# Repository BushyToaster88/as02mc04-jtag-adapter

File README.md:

# AS02MC04 JTAG adapter for the Digilent JTAG-HS3

A small board that lets a Digilent JTAG-HS3 plug straight onto the 6-pin JTAG header (J4)
of the Alibaba Cloud AS02MC04 FPGA card (label PN YZQT-02337-101, Xilinx Kintex UltraScale+ XCKU3P).

> **Status, 2026-11-13:** the first five boards are on order from JLCPCB and have not arrived.
> Nothing here has been tested on real hardware yet. Write-up:
> <https://www.exulan.com/blog/2026-11-13-as02mc04-jtag-adapter>

The HS3 has a 2x7, 2.00 mm Xilinx plug. The card has a 1x6, 2.54 mm pin header with a different
pin order and no keying. This board converts one to the other, takes the HS3's reference voltage
from the card's own 1V8 pin, and survives being plugged on the wrong way round.

| | |
|---|---|
| Revision | C, 2026-11-11 |
| Board | 24.0 x 29.55 mm, 2 layers, 1.6 mm, all parts on one side |
| Made by | JLCPCB, economic assembly, arrives ready to use (no soldering) |
| Card side | J2, right-angle 1x6 socket on the bottom edge, plugs onto J4 |
| Probe side | J1, keyed and shrouded Molex 87832-1420, the header the HS3 is made for |
| JTAG voltage | 1.8 V only, taken from the card |

## How it sits on the card

The adapter stands upright on J4. The side with the parts (front) points away from the card,
past its rear edge, and so does the HS3. The side with the pin names (back) faces the heatsink.

J4 is at the rear end of the card (the end away from the bracket), on the heatsink side. Seen from
that side with the rear edge toward you, the card's silkscreen reads `GND TDI TDO TDK TMS 1`, with
`1V8` printed sideways next to pin 1. `TDK` is the card's spelling of TCK.

Space needed: the top of the adapter is about 32 mm above the card, and the HS3 sticks out roughly
35 mm past the card's rear edge, plus the USB plug and the bend of its cable.

## Pin map

| HS3 / J1 pin | Signal | Through | J2 pin | Card J4 pin | Card silkscreen |
|---|---|---|---|---|---|
| 2 | VREF (HS3 buffer supply) | R9, 4.7 ohm 0.75 W | 1 | 1 | 1V8 |
| 4 | TMS | R1, 22 ohm | 2 | 2 | TMS |
| 6 | TCK | R2, 22 ohm | 3 | 3 | TDK |
| 8 | TDO (card to HS3) | R3, 22 ohm | 4 | 4 | TDO |
| 10 | TDI | R4, 22 ohm | 5 | 5 | TDI |
| 1, 3, 5, 7, 9, 11, 13 | GND | Q1 (reverse protection) | 6 | 6 | GND |
| 12, 14 | not connected | | | | |

## Check the connector pitch first

`docs/pitch_gauge.pdf` is a 1:1 print sheet for both connectors. Print it at 100 %, check the
100 mm bar with a ruler, then hold the card header against rows A and B and the HS3 plug against
patterns C and D. The adapter is built for row A (2.54 mm) and pattern C (2.00 mm).
Checked against the real card and HS3 on 2026-11-11: both match.

## Ordering from JLCPCB

Everything JLCPCB needs is in `fab/`:

| File | Used for |
|---|---|
| `fab/as02mc04_jtag_hs3-gerbers.zip` | the bare board |
| `fab/as02mc04_jtag_hs3-bom.csv` | assembly: bill of materials with LCSC part numbers |
| `fab/as02mc04_jtag_hs3-cpl.csv` | assembly: where each part goes |

1. On jlcpcb.com start a PCB order and upload `as02mc04_jtag_hs3-gerbers.zip`. It should detect a
   2-layer board of 24 x 29.55 mm.
2. Board options (names as on JLCPCB's form in November 2026). Leave everything else as it is.

   | Option | Choose |
   |---|---|
   | Base Material, Layers | FR-4, 2 |
   | PCB Qty, Delivery Format | 5, Single PCB |
   | PCB Thickness, Outer Copper Weight | 1.6mm, 1 oz |
   | PCB Color, Silkscreen | Green (any colour works), White |
   | Surface Finish | LeadFree HASL, or HASL(with lead). Not OSP, which the form may preselect |
   | Via Covering | Tented |
   | Board Outline Tolerance | ±0.2mm (Regular). The precision option needs a board of at least 50 x 50 mm |
   | Mark on PCB | Remove Mark |
   | PCB Build Time | the line that shows A$0.00 (2 days; with assembly on, the form picks "24 hours, PCBA Only" itself) |

   Do not click the "High Precision PCB" layer counts: that is JLCPCB's product for boards of 6 or
   more layers. If you did, reload the page, because it can leave an expensive filled-via option on.
3. Turn on PCB Assembly: PCBA Type "Economic", Assembly Side "Top Side", Tooling holes "Added by
   JLCPCB", Parts Selection "By Customer". For PCBA Qty choose 5 or 2 (the rest arrive as bare
   boards with no parts). Set "Confirm Parts Placement" to Yes and, in the box that pops up, tick
   "Do not confirm automatically": otherwise JLCPCB approves its own placement drawing for you
   after 72 hours. With it ticked, the order waits until you have looked at the drawing.
4. Upload the BOM and CPL files. All 12 lines should match a part and show stock. Four lines are
   marked as extended-library parts (J1, J2, Q1, R9). The three surface mount ones (J1, Q1, R9)
   carry a one-off loading fee each. J2 is a through-hole part that JLCPCB fits and solders by
   hand, for a labour fee and a charge per joint.
5. In the placement preview, check these before paying:
   * **J1** (the big black header): the gap in its wall (the key slot) must be on the side toward
     the 3 mm hole and the small test holes, next to the white bar printed on the board.
     If JLCPCB shows it turned half a turn, rotate it by 180 degrees in the preview. This is the one
     orientation the pad pattern cannot show, and it matters: a header fitted backwards would short
     the HS3's ground pins to the 1.8 V line.
   * **J2** (the socket): its body must lie over the large empty area, with the openings at the
     board edge that has the cut-off corner. It must not point up toward J1.
   * **Q1**: the side with one leg points toward J2, the side with two legs toward J1.
   * **D2**: the marked (cathode) end points toward the bottom edge, away from R8.

   This is what JLCPCB's preview showed for these files on 2026-11-11. The pink triangle marks pin 1
   of J1, the pink dot pin 1 of Q1, and the pink plus the anode of D2:

6. In the assembly options, under Advanced Options, set "Assembly remark" to Yes and paste this:

   > J1 (C492354): keep the rotation from the CPL. The key slot of the shroud faces the board edge
   > with the 3 mm hole. Do not turn it by 180 degrees.
   > J2 (C54876735): symmetric 1x6 right-angle socket with no polarity. Its body lies on the board
   > with the openings at the edge that has the chamfered corner. Do not rotate it.
   > If you add rails or mouse-bite tabs, keep them off the J2 edge (the edge with the chamfered corner).

Cost: on 2026-11-11 JLCPCB's order page quoted A$58.29 for 5 boards with all 5 assembled
(lead-free finish, placement confirmation on), before shipping and tax. That is A$7.40 for the
boards and A$50.89 for assembly, of which A$14.76 is parts and the rest fees. DHL Express was
estimated at A$31.03 on top. Most of the fees are fixed, so assembling only 2 saves little. The
quote on the order page on the day is the real number.

The boards may arrive joined to a break-off rail that JLCPCB adds for its machines. Snap it off
and file the edge smooth, or pay for "Depanel boards & edge rail before delivery" in the assembly
options (JLCPCB's form says it adds a day). To snap a rail off, grip the rail with flat pliers
right beside the board and bend the rail, not the board: C1 and C2 sit close to the right-hand
edge, and ceramic capacitors can crack when the board under them flexes.

If J2 is out of stock, these are the same kind of socket (8.5 mm body, 2.54 mm pitch): C55629861,
C2932681, C22436147. Compare the datasheet with the J2 footprint before swapping, and change the
LCSC number in the BOM file.

## Before first use

1. Look at J1. The slot in its wall must be on the same side as the white bar printed next to it
   (toward the test holes). If it is on the other side, do not use the board.
2. Look at D2, the small LED next to the word `REVERSED` (a magnifier helps). The small green mark
   on its top face must be at the end toward the bottom edge (the edge the socket opens onto). If
   the mark is at the other end, the LED was fitted backwards. The adapter still works, but the
   light then means the opposite of what this guide says, so ignore it on that board.
3. Look at the bottom edge. If the factory left a small nub of board material there, file it flat.
4. With a multimeter on resistance, and the adapter not plugged into anything, check the two
   hand-soldered socket pins where a solder bridge to the ground copper would bypass a protection.
   The pins are the solder points on the back, labelled `1V8` and `GND`. Two different points
   carry the name `GND`: the `GND` solder pin at the socket is the card's ground, and the `GND`
   test hole on the top edge is the adapter's own ground behind Q1.
   * red lead on the `1V8` solder pin, black on the `GND` test hole: settles at about 10 kilohm.
   * `1V8` solder pin to the `GND` solder pin: anything from a few kilohm to about a megohm,
     depending on the meter and which way round the leads are.
   * `GND` solder pin to the `GND` test hole: a few hundred ohms to about a megohm, depending on
     the meter and the lead direction, because Q1 has a diode inside that conducts one way.

   A reading under 100 ohm on any of the three means a solder bridge or a faulty part. Do not use
   that board.
5. With the card powered and nothing connected to J4, measure the card's pin 1 (`1V8`) against its
   `GND` pin. Expect about 1.8 V.
6. The pin at the `1V8` end of J4 on some cards is slightly bent. Straighten it gently so all six
   pins are in line.

## Using it

The one rule that protects the card: **take the adapter off the card to plug or unplug the HS3,
and to plug or unplug the USB cable at the HS3.** J4 is a surface-mount header held by six small
solder joints, and the HS3 on the adapter is a long lever. Its micro-USB socket is at the far end,
in line with the plug, so pushing or pulling a plug at either end of the HS3 pushes sideways on
J4. The reminder printed on the back of the board names only the HS3; treat its USB socket the
same way. While the adapter is on the card, connect and disconnect the USB cable at the PC end
only.

### Plugged straight onto the card (bench or riser)

1. Switch the card off and touch the PC case or another grounded metal part first. The test
   holes on the top edge and the solder pins on the back connect straight to FPGA pins, so hold the
   adapter by its side edges. (The adapter tolerates being plugged onto a powered card, but
   switched off is safer: a slip cannot short two live pins.)
2. Plug the HS3 into the adapter, with the adapter lying flat on the bench. The HS3 only goes in
   one way. Plug the micro-USB cable into the HS3 now as well, and leave its other end free.
3. Hold the adapter with the HS3 pointing away from the card and lower it onto J4. The `GND` end of
   the adapter goes on the card's `GND` pin and the cut-off `1V8` corner on the card's `1V8` pin.
   Support the card from below near J4 with your other hand, or rest that end of the card on the
   bench. Press on the top edge of the adapter, straight down, until it stops. The socket can stop
   a fraction of a millimetre above the plastic base of the header, because the board edge reaches
   slightly past the socket. That is fine: do not force it further.
   Look from the side and count: all six pins must be in the socket, none left over at either end.
4. Plug the free end of the USB cable into the PC, then switch the card on. Fix the USB cable to
   the bench or the case close to the HS3 and leave a little slack, so a pull on the cable never
   reaches the card.
5. To remove: switch off, unplug the USB cable at the PC, then lift the adapter and the HS3
   together, straight up (a loop of cord through the pull hole helps). Separate them, and the
   micro-USB plug, on the bench.

Never let the HS3 hang by its cable.

### With a jumper cable (inside a PC, or when space is tight)

Use a 6-way male-to-female 2.54 mm jumper cable, 20 cm or shorter. The male ends go into J2, the
female ends onto J4, in the same order, so `1V8` meets `1V8` and `GND` meets `GND`. A cable with a
single 1x6 housing at each end is the easiest to get right. This is also the better choice for
anything longer than a quick session, because nothing heavy hangs on J4.

Wire it with the card switched off, and check every wire against the labels before switching on.
The reverse protection covers the whole 6-way connection turned end for end. It does not cover
single wires that are crossed. The one dangerous mix-up is the adapter's `GND` wire on the card's
`1V8` pin while the adapter's `1V8` wire sits on a signal pin. If the HS3 is then on a PC that
shares its ground with the card, the signal pin's weak pull-up can turn Q1 partly on, and Q1
passes current from the card's 1.8 V rail into the USB ground: a few tens of milliamps with a
typical part, up to about an amp in the worst case (a simulation, not a measurement). A single
1x6 housing at each end rules this out.

### Software

Use 15 MHz or lower when plugged straight on, and 6 MHz with a jumper cable. Do not use the HS3's
30 MHz setting: the timing of the HS3 and the FPGA together does not guarantee it. If the device
is found only sometimes, go lower (3 MHz, then 1 MHz).

In Vivado the HS3 opens at 15 MHz by default. To set 6 MHz:

```tcl
open_hw_manager
connect_hw_server
current_hw_target [get_hw_targets */xilinx_tcf/Digilent/*]
set_property PARAM.FREQUENCY 6000000 [current_hw_target]
open_hw_target
```

With openFPGALoader:

```bash
openFPGALoader -c digilent_hs3 --freq 6000000 --detect
```

The chain holds one device: XCKU3P, IDCODE 0x04A63093. Seeing that IDCODE is the real "it works"
indicator.

## If it does not work

| What you see | Likely cause |
|---|---|
| Red light next to `REVERSED` is on, no device found | The 6-pin connection is reversed. Nothing is damaged. Turn it round. |
| No device found, no light | Card not powered, socket one pin off, or reversed (the light is dim and can be missed). |
| Red light is on, but the device is found | D2 was fitted backwards at the factory (see "Before first use"). Ignore the light on that board. |
| Device found only sometimes | Lower the JTAG clock, shorten the cable. |

The red light is a best effort: it runs from 1.8 V, which is barely enough for a red LED, so it
is dim and on some boards may not be visible at all. No light is not proof that the orientation
is right.

To check the supply, measure between the test holes `VREF` and `GND` with everything connected and
the card on. Expect a reading within about 0.1 V of the card's own `1V8` pin, so 1.70 V or more on
a 1.8 V rail. If it reads under 1.65 V, the HS3 is below its minimum: check the card's `1V8` pin
and lower the JTAG clock, since the HS3 draws more at higher clock rates. If it reads about half a
volt low while the card's own pin is fine, Q1 is not switching on and that board is faulty.

## What the parts do

* **R9 (4.7 ohm, 0.75 W)** sits between the card's 1V8 pin and everything else on the adapter.
  Whatever goes wrong behind it, the card's 1.8 V rail cannot be shorted hard: the most that can
  flow is about 0.38 A. In a dead short R9 turns about 0.7 W into heat. It is a 0.75 W part, so
  it runs hot instead of burning out: a thermal model (not a measurement) gives roughly 105 to
  145 C at room temperature against a limit of 155 C, and more at the top of the 1.8 V tolerance or
  inside a warm case, where it can pass that limit. Do not leave a fault connected. The only
  copper ahead of R9 is socket pin 1, a 2 mm link and R9's own input pad.
* **Q1** is a MOSFET in the ground wire. It only conducts when 1.8 V arrives on the correct pin.
  If the 6-pin connection is reversed, the card's 1.8 V would otherwise be shorted to PC ground
  through the HS3's USB cable. Q1 blocks that. **R5** feeds its gate and **R10** bleeds static
  across it.
* The ground copper is kept 0.5 mm back from the two socket pins that matter most, `1V8` and
  `GND`, on both faces. A solder bridge from one of them to the ground copper would bypass R9 or
  Q1, which is what the meter check under "Before first use" looks for.
* **R1 to R4 (22 ohm)** are series resistors on the four JTAG signals. The HS3 already has
  100 ohm inside, so these mostly give a place to probe, cut or change a line.
* **C1, C2** decouple the HS3's buffer supply. **R7** (10 kilohm) discharges them when unplugged
  and holds the gate of Q1 low whenever the 1.8 V is absent.
* **D2 and R8** are the reversed-connection light.
* **Test holes** on the top edge (`GND TDI TDO`, then `TCK TMS VREF`) are for a scope or logic
  analyzer. Each group takes a 3-pin 2.54 mm header if you want to solder one in. They are not a
  second card port: `VREF` is the 1.8 V after R9 and `GND` is the adapter ground after Q1.
* The **pull hole** takes a loop of cord for lifting the adapter straight off the header.

## Limits

* 1.8 V JTAG only. The FPGA's configuration bank must not see more than 2.35 V.
* The card must be powered through its PCIe connector (slot or powered riser) for JTAG to work.
* Standing on the card the adapter is about 32 mm tall and the HS3 points out past the rear edge,
  so it will not fit next to a neighbouring card or a drive cage. Use the cable there.
* The reverse protection covers the 6-pin connection turned round. It does not notice a socket
  that is one pin off to the side, so count the pins when seating it, and it does not cover
  single crossed wires in a jumper cable (see "With a jumper cable"). It was worked out for the
  HS3, whose signal pins have no clamp to its Vref pin. Do not assume it holds for another probe.
* Nothing protects against a J1 header that the factory fitted backwards. That is what the checks
  in the placement preview and under "Before first use" are for.

## Rebuilding the design

The KiCad 10 project is in `hw/`. It is generated from one netlist file, `tools/design.py`, so the
schematic and the board cannot disagree.

The scripts need KiCad 10 (for `kicad-cli` and the `pcbnew` Python module) and a virtual
environment in `.venv` that can see the system packages:

```bash
python -m venv --system-site-packages .venv
```

```bash
.venv/bin/pip install sexpdata pillow
```

```bash
tools/build.sh
```

regenerates the schematic and board and runs KiCad's electrical and design rule checks plus the
project's own checks: the netlist against `design.py`, the physical pin order and pitch of both
connectors, the position of the socket at the board edge, the ground copper held back from the
two critical socket pins, the silkscreen against JLCPCB's printing limits (1.0 mm characters,
0.15 mm lines, no text on a pad, a hole or an edge), and every label against the net it sits
beside.

```bash
tools/fab.sh
```

exports the JLCPCB files and verifies them (drill counts, outline, and each part's rotation against
JLCPCB's own footprint).

```bash
tools/render.sh
```

redraws the layout plots, the 3D renders and the showcase picture in `docs/img/`, and
`docs/schematic.pdf`. The side view `docs/img/how_it_sits.png` comes from
`.venv/bin/python tools/gen_diagram.py`.

```bash
.venv/bin/python tools/gen_gauge.py
```

redraws the pitch gauge sheet.

## Licence

The design is released under the CERN Open Hardware Licence Version 2, Permissive
(CERN-OHL-P v2), see `LICENSE`. The footprints, symbols and 3D models in `hw/lib/jlc.*` were
converted from the EasyEDA/LCSC part library with easyeda2kicad and remain subject to their
original terms.

The design was produced by Claude (Anthropic) working with the owner of this repository.

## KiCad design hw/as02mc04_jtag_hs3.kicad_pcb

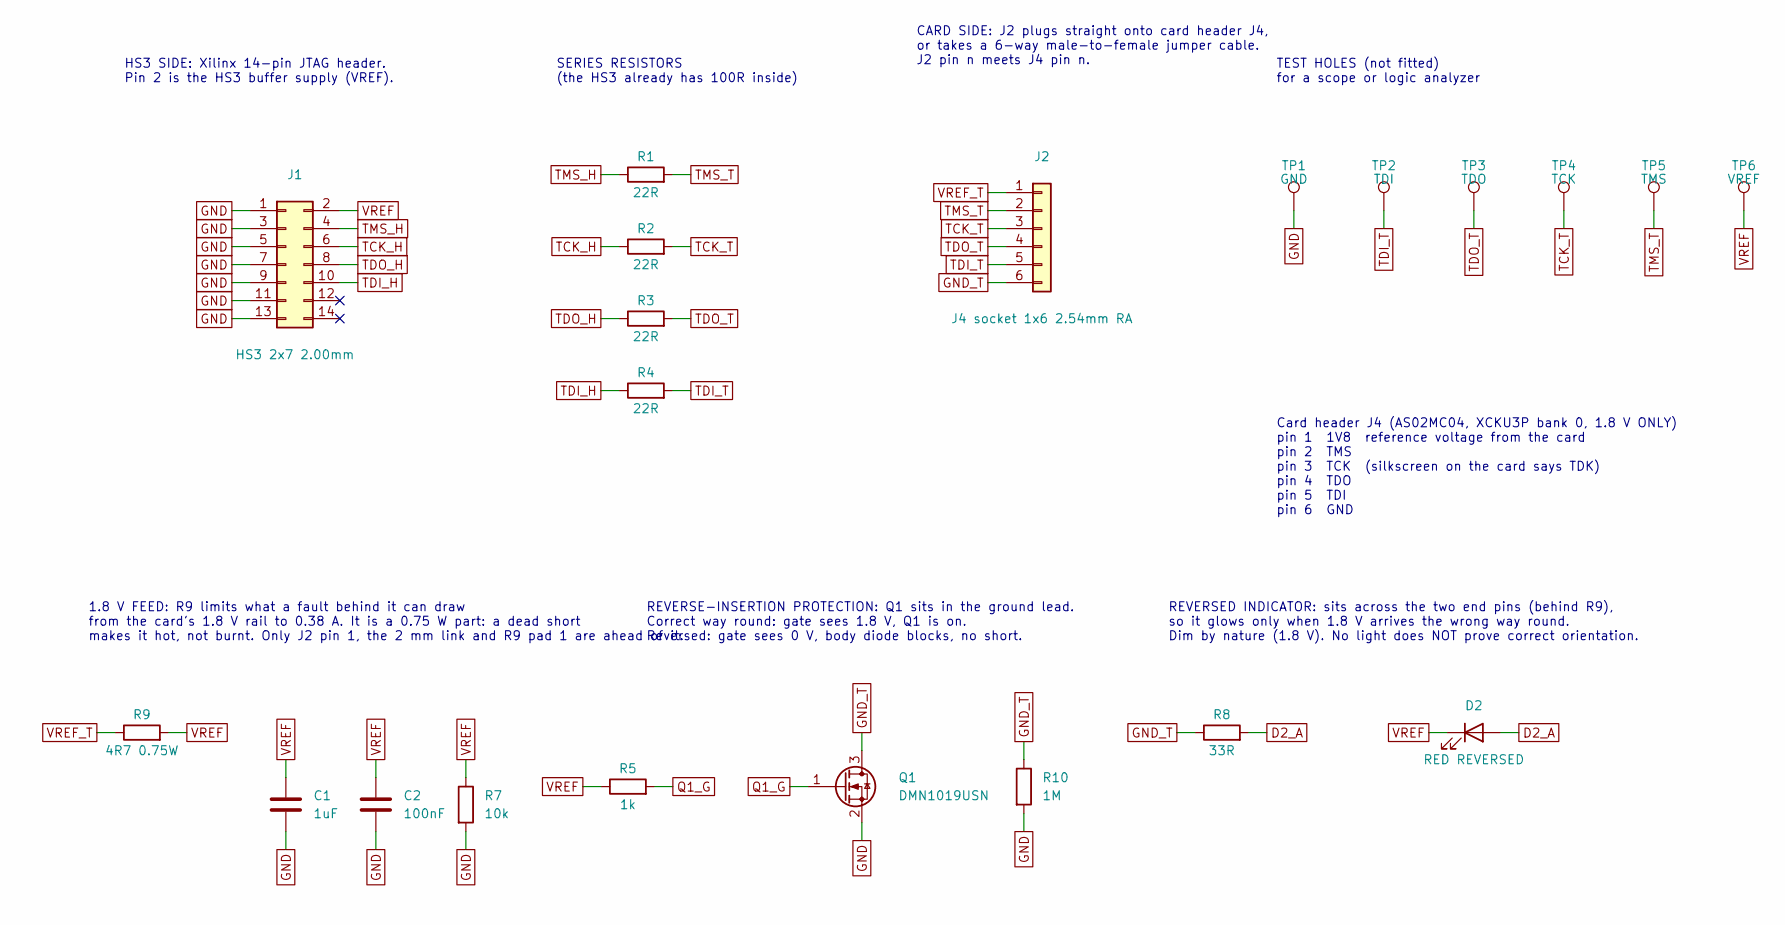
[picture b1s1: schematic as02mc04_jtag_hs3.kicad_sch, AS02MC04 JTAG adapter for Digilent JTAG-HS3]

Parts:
C1: 1uF; C_0603_1608Metric; MPN CL10A105KB8NNNC; LCSC C15849
C2: 100nF; C_0603_1608Metric; MPN CC0603KRX7R9BB104; LCSC C14663
D2: RED REVERSED; LED_0603_1608Metric; MPN KT-0603R; LCSC C2286
J1: HS3 2x7 2.00mm; Molex_8783214xx_2x07_P2.0mm_Header_Vertical_Polarized_Mount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; MPN 87832-1420; LCSC C492354
J2: J4 socket 1x6 2.54mm RA; Socket_1x06_P2.54mm_RA_J4order; MPN PM2.54-1x6PWZ-H8.5; LCSC C54876735
Q1: DMN1019USN; SC-59; MPN DMN1019USN-7; LCSC C145103
R1, R2, R3, R4: 22R; R_0603_1608Metric; MPN 0603WAF220JT5E; LCSC C23345
R5: 1k; R_0603_1608Metric; MPN 0603WAF1001T5E; LCSC C21190
R7: 10k; R_0603_1608Metric; MPN 0603WAF1002T5E; LCSC C25804
R8: 33R; R_0603_1608Metric; MPN 0603WAF330JT5E; LCSC C23140
R9: 4R7 0.75W; R_1206_3216Metric; MPN CRCW12064R70FKEAHP; LCSC C313986
R10: 1M; R_0603_1608Metric; MPN 0603WAF1004T5E; LCSC C22935
TP1: GND; TestHole_D1.7mm_Drill1.0mm
TP2: TDI; TestHole_D1.7mm_Drill1.0mm
TP3: TDO; TestHole_D1.7mm_Drill1.0mm
TP4: TCK; TestHole_D1.7mm_Drill1.0mm
TP5: TMS; TestHole_D1.7mm_Drill1.0mm
TP6: VREF; TestHole_D1.7mm_Drill1.0mm

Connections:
D2_A: D2.2 (A), R8.2
GND: C1.2, C2.2, J1.1, J1.3, J1.5, J1.7, J1.9, J1.11, J1.13, Q1.2 (S), R7.2, R10.2, TP1.1
GND_T: J2.6, Q1.3 (D), R8.1, R10.1
Q1_G: Q1.1 (G), R5.2
TCK_H: J1.6, R2.1
TCK_T: J2.3, R2.2, TP4.1
TDI_H: J1.10, R4.1
TDI_T: J2.5, R4.2, TP2.1
TDO_H: J1.8, R3.1
TDO_T: J2.4, R3.2, TP3.1
TMS_H: J1.4, R1.1
TMS_T: J2.2, R1.2, TP5.1
VREF: C1.1, C2.1, D2.1 (K), J1.2, R5.1, R7.1, R9.2, TP6.1
VREF_T: J2.1, R9.1

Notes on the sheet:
SERIES RESISTORS (the HS3 already has 100R inside)
1.8 V FEED: R9 limits what a fault behind it can draw from the card's 1.8 V rail to 0.38 A. It is a 0.75 W part: a dead short makes it hot, not burnt. Only J2 pin 1, the 2 mm link and R9 pad 1 are ahead of it.
CARD SIDE: J2 plugs straight onto card header J4, or takes a 6-way male-to-female jumper cable. J2 pin n meets J4 pin n.
TEST HOLES (not fitted) for a scope or logic analyzer
Card header J4 (AS02MC04, XCKU3P bank 0, 1.8 V ONLY) pin 1 1V8 reference voltage from the card pin 2 TMS pin 3 TCK (silkscreen on the card says TDK) pin 4 TDO pin 5 TDI pin 6 GND
HS3 SIDE: Xilinx 14-pin JTAG header. Pin 2 is the HS3 buffer supply (VREF).
REVERSED INDICATOR: sits across the two end pins (behind R9), so it glows only when 1.8 V arrives the wrong way round. Dim by nature (1.8 V). No light does NOT prove correct orientation.
REVERSE-INSERTION PROTECTION: Q1 sits in the ground lead. Correct way round: gate sees 1.8 V, Q1 is on. Reversed: gate sees 0 V, body diode blocks, no short.

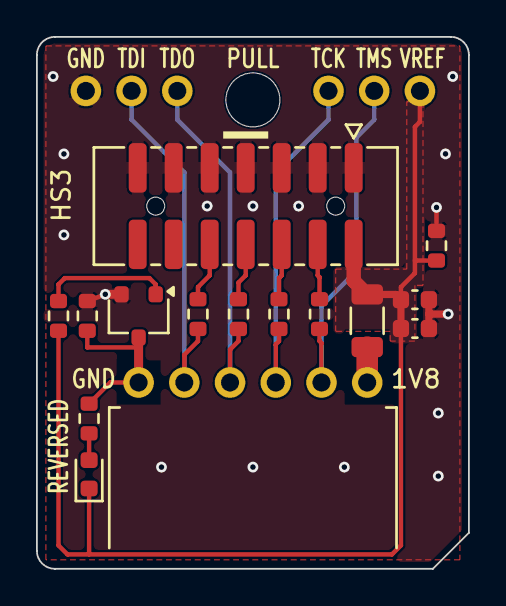
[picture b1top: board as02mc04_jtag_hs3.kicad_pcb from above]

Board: 2 copper layers, 24.0 x 29.6 mm, 22 parts (0 on the bottom side), 14 nets.

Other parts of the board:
H1: PULL; PullHole_3.0mm_NPTH

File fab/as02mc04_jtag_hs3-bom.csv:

Comment,Designator,Footprint,LCSC Part #
1uF (CL10A105KB8NNNC),C1,C_0603_1608Metric,C15849
100nF (CC0603KRX7R9BB104),C2,C_0603_1608Metric,C14663
RED REVERSED (KT-0603R),D2,LED_0603_1608Metric,C2286
HS3 2x7 2.00mm (87832-1420),J1,Molex_8783214xx_2x07_P2.0mm_Header_Vertical_Polarized_MountingPegs,C492354
J4 socket 1x6 2.54mm RA (PM2.54-1x6PWZ-H8.5),J2,Socket_1x06_P2.54mm_RA_J4order,C54876735
DMN1019USN (DMN1019USN-7),Q1,SC-59,C145103
22R (0603WAF220JT5E),"R1,R2,R3,R4",R_0603_1608Metric,C23345
1k (0603WAF1001T5E),R5,R_0603_1608Metric,C21190
10k (0603WAF1002T5E),R7,R_0603_1608Metric,C25804
33R (0603WAF330JT5E),R8,R_0603_1608Metric,C23140
4R7 0.75W (CRCW12064R70FKEAHP),R9,R_1206_3216Metric,C313986
1M (0603WAF1004T5E),R10,R_0603_1608Metric,C22935

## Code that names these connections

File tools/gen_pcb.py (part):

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        return [(x0, y0), (x0, yk), (x1, yk + abs(x1 - x0)), (x1, y1)]

    # ---- HS3 side: J1 even pads down to the series resistors
    for jpin, r, net in ((4, "R1", "TMS_H"), (6, "R2", "TCK_H"), (8, "R3", "TDO_H"), (10, "R4", "TDI_H")):
        tr(net, dogleg(p("J1", jpin), p(r, 1), 13.25))

    # ---- card side: resistors down to J2
    for r, jpin, net in (("R1", 2, "TMS_T"), ("R2", 3, "TCK_T"), ("R3", 4, "TDO_T"), ("R4", 5, "TDI_T")):
        tr(net, dogleg(p(r, 2), p("J2", jpin), 16.9))

    # ---- 1.8 V: J2 pad 1 -> R9 -> HS3 pin 2, decoupling, bleeder, test hole.
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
